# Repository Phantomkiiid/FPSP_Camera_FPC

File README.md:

# FPSP_Camera_FPC
This repo contains FPC schematics of the newly developed FPSP camera project on an FPC board, aiming for super-high-speed parallel image processing.

## Repository Structure
| Directory | Use |
| --------- | --- |
| archive_old/ | Archived initial design (**not working**) |
| custom_fp/ | Footprint from external libraries |
| docs/ | Documentation gathered from external sources |

## TODO
- [ ] RP2350 Power Supply Layout
- [ ] Add Proper Power Sequencing
- [ ] Source RP2354 A4
- [ ] Source B2B Connector
- [ ] B2B Connector Pinout + Layout
- [ ] HSTX Layout

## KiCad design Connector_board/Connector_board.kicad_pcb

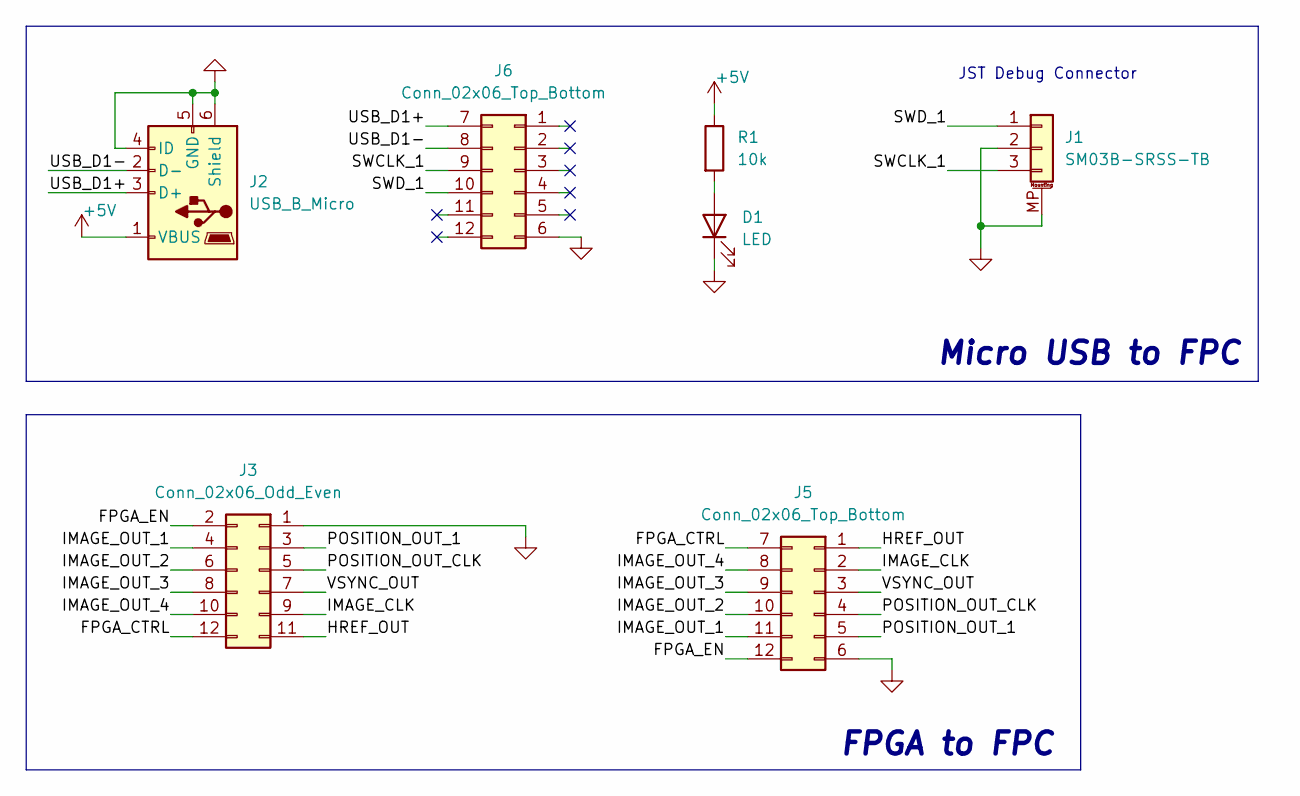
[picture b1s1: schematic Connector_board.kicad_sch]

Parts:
D1: LED; D_0603_1608Metric
J1: SM03B-SRSS-TB; JST_SH_SM03B-SRSS-TB_1x03-1MP_P1.00mm_Horizontal
J2: USB_B_Micro; USB_Micro-B_Molex_47346-0001
J3: Conn_02x06_Odd_Even; PinHeader_2x06_P2.54mm_Vertical
J5, J6: Conn_02x06_Top_Bottom; CON_5035521222
R1: 10k; R_0603_1608Metric_Pad0.98x0.95mm_HandSolder

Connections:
+5V: J2.1 (VBUS), R1.1
/FPGA_CTRL: J3.12, J5.7
/FPGA_EN: J3.2, J5.12
/HREF_OUT: J3.11, J5.1
/IMAGE_CLK: J3.9, J5.2
/IMAGE_OUT_1: J3.4, J5.11
/IMAGE_OUT_2: J3.6, J5.10
/IMAGE_OUT_3: J3.8, J5.9
/IMAGE_OUT_4: J3.10, J5.8
/POSITION_OUT_1: J3.3, J5.5
/POSITION_OUT_CLK: J3.5, J5.4
/SWCLK_1: J1.3, J6.9
/SWD_1: J1.1, J6.10
/USB_D1+: J2.3 (D+), J6.7
/USB_D1-: J2.2 (D-), J6.8
/VSYNC_OUT: J3.7, J5.3
GND: D1.1 (K), J1.2, J1.MP (MountPin), J2.4 (ID), J2.5 (GND), J2.6 (Shield), J3.1, J5.6, J6.6
unnamed: D1.2 (A), R1.2

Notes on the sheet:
FPGA to FPC
Micro USB to FPC
JST Debug Connector

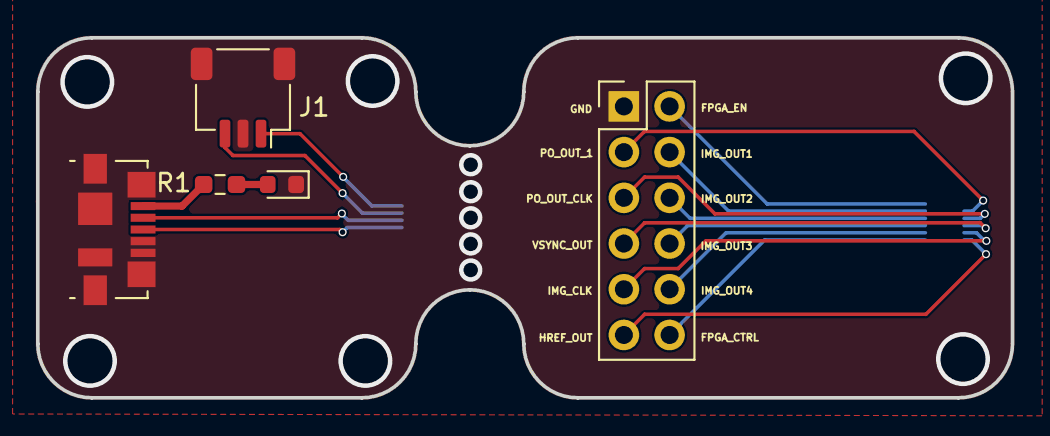
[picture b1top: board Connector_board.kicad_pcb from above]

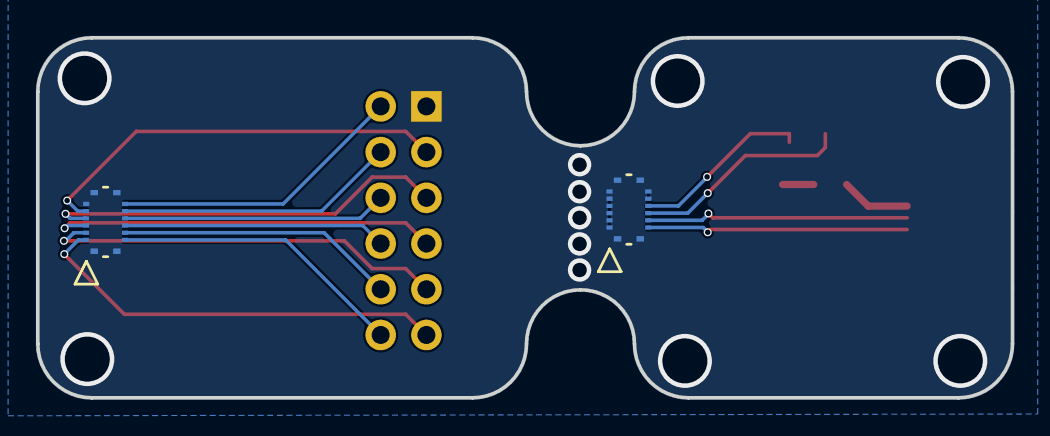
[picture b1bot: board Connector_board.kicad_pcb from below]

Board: 2 copper layers, 54.2 x 20.0 mm, 7 parts (2 on the bottom side), 18 nets.

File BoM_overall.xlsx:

Part Name | Series Number / Description | Quantity | Source | Unit Price (GBP) | Order Code / Mouser No | Link
USB_B_Micro | USB_Micro-B_Molex_47346-0001 | 5 | Farnell | 1.2 | 1568026 | https://uk.farnell.com/molex/47346-0001/micro-usb-conn-2-0-t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
Conn_02x07_Counter_Clockwise | Molex_SlimStack_502426-1430_2x07_P0.40mm_Vertical | 10 | Farnell | 0.86799999999999999 | 3500584 | https://uk.farnell.com/molex/502426-1430/mezzanine-conn-rcpt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
Conn_02x07_Counter_Clockwise | Molex_SlimStack_502430-1430_2x07_P0.40mm_Vertical | 10 | Farnell | 0.46500000000000002 | 3911710 | https://uk.farnell.com/molex/502430-1430/mezzanine-conn-hdr-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
Switch (slide) | CAS-120TA1 | 10 | Farnell | 1.1832 | 2854716 | https://uk.farnell.com/nidec-copal-electronics/cas-120ta/sli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
Push Button | PTS526SM15SMTR2 LFS | 10 | Mouser | 0.12 | 611-PTS526SM15SMTR2L | https://www.mouser.co.uk/ProductDetail/CK/PTS526SM15SMTR2-LF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
SM03B-SRSS-TB | JST_SH_SM03B-SRSS-TB_1x03-1MP_P1.00mm_Horizontal | 5 | Farnell | 0.52 | 1679118 | https://uk.farnell.com/stmicroelectronics/lsm6dsltr/inemo-in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
IMU | LSM6DSLTR | 5 | Farnell | 7.8840000000000003 | 4572492 | https://uk.farnell.com/tdk/icm-45686/mems-module-6-axis-1-71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
LDO | TLV73315PDRV | 5 | Mouser | 0.44 | 595-TLV73315PQDRVRQ1 | https://www.mouser.co.uk/ProductDetail/Texas-Instruments/TLV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
MCU | RP2354A | 5 | Mouser | 0.751 | 358-SC151113 | https://www.mouser.co.uk/ProductDetail/Raspberry-Pi/SC151113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
Mems | SiT8008BI-13-33E-12.000000G | 5 | Mouser | 0.72099999999999997 | 788-8008BI1333E12G | https://www.mouser.co.uk/ProductDetail/SiTime/SiT8008BI-13-3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
FPC socket | molex 52435-2471 | 10 | Farnell | 2.3519999999999999 | 2396220 | https://uk.farnell.com/molex/52435-2471/connector-ffc-fpc-24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
Camera | OV5640 - 24pin fpc | 2 | Ali | N/A | N/A | https://www.aliexpress.com/p/tesla-landing/index.html?UTABTe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
2.54mm pin header: from UCL
0603 R&C: from UCL

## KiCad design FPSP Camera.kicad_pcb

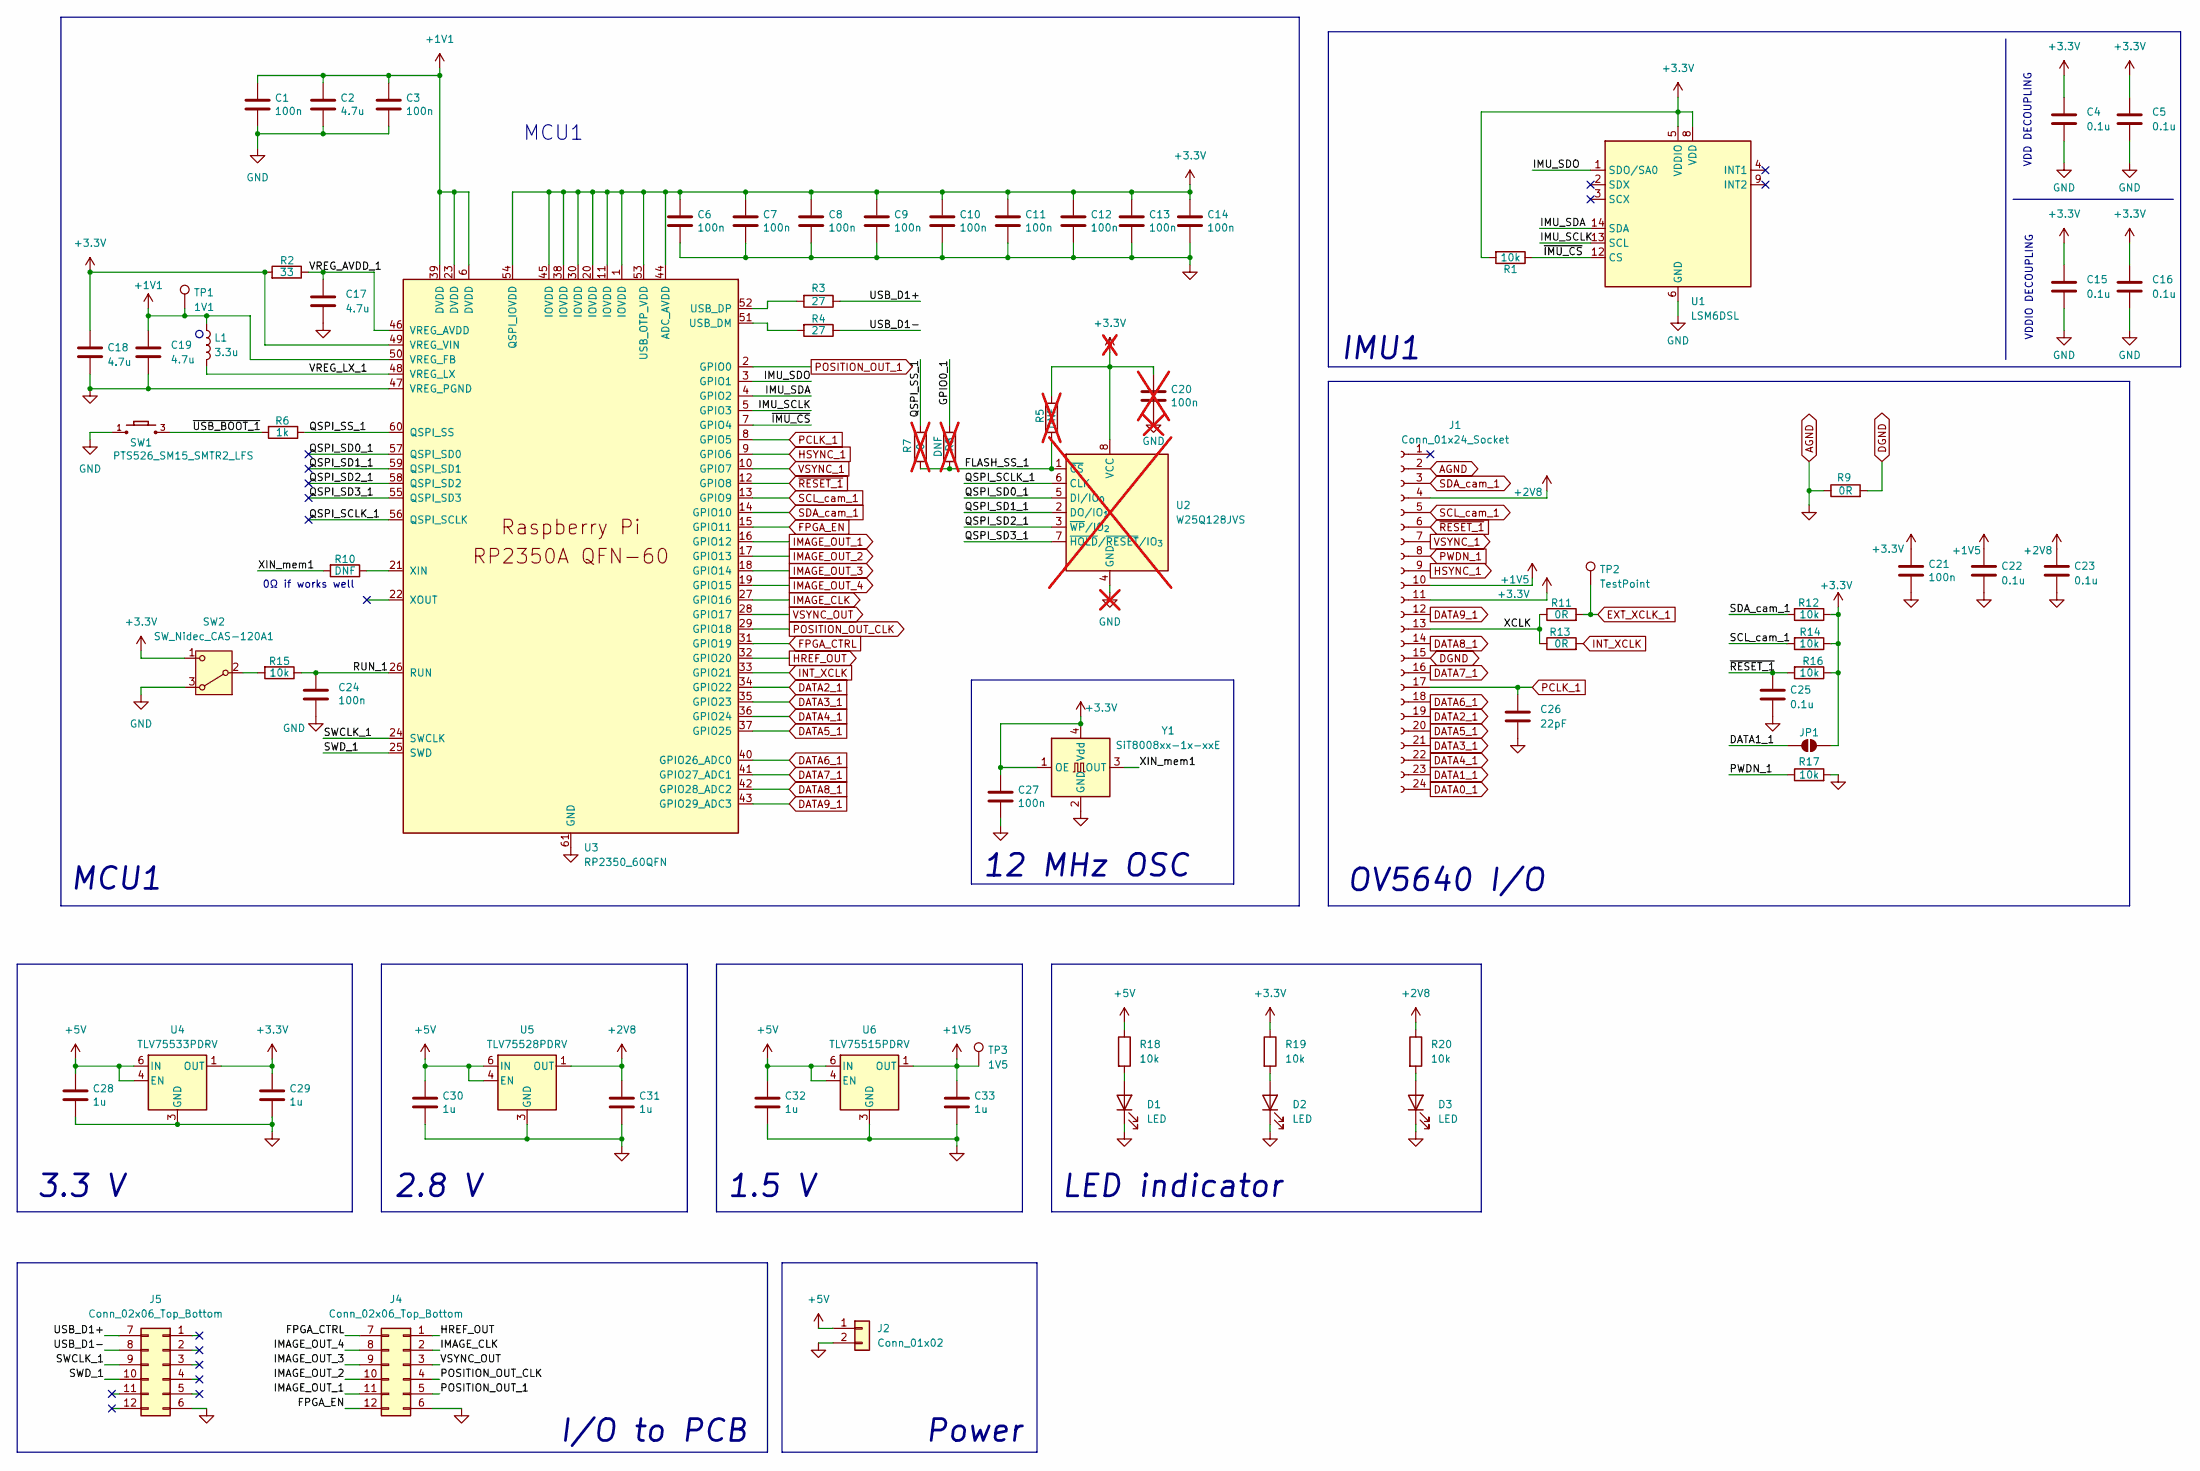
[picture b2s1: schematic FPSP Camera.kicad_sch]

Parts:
C1, C3, C6, C7, C8, C9, C10, C11, C12, C13, C14, C21, C24, C27: 100n; C_0402_1005Metric
C2, C17, C18, C19: 4.7u; C_0402_1005Metric
C4, C5, C15, C16, C22, C23, C25: 0.1u; C_0402_1005Metric
C20: 100n; C_0603_1608Metric_Pad1.08x0.95mm_HandSolder; not fitted
C26: 22pF; C_0402_1005Metric
C28, C29, C30, C31, C32, C33: 1u; C_0402_1005Metric
D1, D2, D3: LED; D_0603_1608Metric
J1: Conn_01x24_Socket; MOLEX_52435-2471
J2: Conn_01x02; PinHeader_1x02_P2.54mm_Vertical
J4, J5: Conn_02x06_Top_Bottom; CON_5035521222
JP1: SolderJumper_2_Open; SolderJumper-2_P1.3mm_Open_RoundedPad1.0x1.5mm
L1: 3.3u; L_pol_2016
R1: 10k; R_0402_1005Metric_Pad0.72x0.64mm_HandSolder
R2: 33; R_0402_1005Metric
R3, R4: 27; R_0402_1005Metric
R5, R8: DNF; R_0603_1608Metric_Pad0.98x0.95mm_HandSolder; not fitted
R6: 1k; R_0402_1005Metric
R7: 0; R_0603_1608Metric_Pad0.98x0.95mm_HandSolder; not fitted
R9, R11, R13: 0R; R_0402_1005Metric
R10: DNF; R_0402_1005Metric
R12, R14, R15, R16, R17, R18, R19, R20: 10k; R_0402_1005Metric
SW1: PTS526_SM15_SMTR2_LFS; PTS526SM15SMTR2LFS; MOUSER_PART_NUMBER 611-PTS526SM15SMTR2L
SW2: SW_Nidec_CAS-120A1; Nidec_Copal_CAS-120A
TP1: 1V1; TestPoint_Pad_D1.0mm
TP2: TestPoint; TestPoint_Pad_D1.0mm
TP3: 1V5; TestPoint_Pad_D1.0mm
U1: LSM6DSL; LGA-14_3x2.5mm_P0.5mm_LayoutBorder3x4y
U2: W25Q128JVS; SOIC-8_5.3x5.3mm_P1.27mm; not fitted
U3: RP2350_60QFN; RP2350-QFN-60-1EP_7x7_P0.4mm_EP3.4x3.4mm_ThermalVias
U4: TLV75533PDRV; WSON-6-1EP_2x2mm_P0.65mm_EP1x1.6mm
U5: TLV75528PDRV; WSON-6-1EP_2x2mm_P0.65mm_EP1x1.6mm
U6: TLV75515PDRV; WSON-6-1EP_2x2mm_P0.65mm_EP1x1.6mm
Y1: SiT8008xx-1x-xxE; Oscillator_SMD_SiT_PQFN-4Pin_2.5x2.0mm

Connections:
+1V1: C1.1, C2.1, C3.1, C19.1, L1.1, TP1.1 (1_1), U3.6 (DVDD), U3.23 (DVDD), U3.39 (DVDD), U3.50 (VREG_FB)
+1V5: C22.1, C33.1, J1.10, TP3.1 (1_1), U6.1 (OUT)
+2V8: C23.1, C31.1, J1.4, R20.1, U5.1 (OUT)
+3.3V: C4.1, C5.1, C6.1, C7.1, C8.1, C9.1, C10.1, C11.1, C12.1, C13.1, C14.1, C15.1, C16.1, C18.1, C20.1, C21.1, C27.1, C29.1, J1.11, JP1.2 (B), R1.2, R2.2, R5.1, R12.1, R14.1, R16.1, R19.1, SW2.1 (C), U1.5 (VDDIO), U1.8 (VDD), U2.8 (VCC), U3.1 (IOVDD), U3.11 (IOVDD), U3.20 (IOVDD), U3.30 (IOVDD), U3.38 (IOVDD), U3.44 (ADC_AVDD), U3.45 (IOVDD), U3.49 (VREG_VIN), U3.53 (USB_OTP_VDD), U3.54 (QSPI_IOVDD), U4.1 (OUT), Y1.1 (OE), Y1.4 (Vdd)
+5V: C28.1, C30.1, C32.1, J2.1, R18.1, U4.4 (EN), U4.6 (IN), U5.4 (EN), U5.6 (IN), U6.4 (EN), U6.6 (IN)
/IMU_SCLK: U1.13 (SCL), U3.5 (GPIO3)
/IMU_SDA: U1.14 (SDA), U3.4 (GPIO2)
/IMU_SDO: U1.1 (SDO/SA0), U3.3 (GPIO1)
/QSPI_SCLK_1: U2.6 (CLK), U3.56 (QSPI_SCLK)
/QSPI_SD0_1: U2.5 (DI/IO_{0}), U3.57 (QSPI_SD0)
/QSPI_SD1_1: U2.2 (DO/IO_{1}), U3.59 (QSPI_SD1)
/QSPI_SD2_1: U2.3 (~WP/IO_{2}), U3.58 (QSPI_SD2)
/QSPI_SD3_1: U2.7 (~HOLD/~RESET/IO_{3}), U3.55 (QSPI_SD3)
/QSPI_SS_1: R6.1, R7.2, U3.60 (QSPI_SS)
/RUN_1: C24.1, R15.1, U3.26 (RUN)
/SWCLK_1: J5.9, U3.24 (SWCLK)
/SWD_1: J5.10, U3.25 (SWD)
/USB_D1+: J5.7, R3.1
/USB_D1-: J5.8, R4.1
/VREG_AVDD_1: C17.1, R2.1, U3.46 (VREG_AVDD)
/VREG_LX_1: L1.2, U3.48 (VREG_LX)
/XCLK: J1.13, R11.1, R13.1
/XIN_mem1: R10.2, Y1.3 (OUT)
/~IMU_CS: R1.1, U1.12 (CS), U3.7 (GPIO4)
/~USB_BOOT_1: R6.2, SW1.3, SW1.4
AGND: C1.2, C2.2, C3.2, C4.2, C5.2, C6.2, C7.2, C8.2, C9.2, C10.2, C11.2, C12.2, C13.2, C14.2, C15.2, C16.2, C17.2, C18.2, C19.2, C20.2, C21.2, C22.2, C23.2, C24.2, C25.2, C26.2, C27.2, C28.2, C29.2, C30.2, C31.2, C32.2, C33.2, D1.1 (K), D2.1 (K), D3.1 (K), J1.2, J1.MP, J2.2, J4.6, J5.6, R9.1, R17.2, SW1.1, SW1.2, SW2.3 (A), U1.6 (GND), U1.7 (GND), U2.4 (GND), U3.47 (VREG_PGND), U3.61 (GND), U4.3 (GND), U4.7 (GND), U5.3 (GND), U5.7 (GND), U6.3 (GND), U6.7 (GND), Y1.2 (GND)
DATA0_1: J1.24
DATA1_1: J1.23, JP1.1 (A)
DATA2_1: J1.19, U3.34 (GPIO22)
DATA3_1: J1.21, U3.35 (GPIO23)
DATA4_1: J1.22, U3.36 (GPIO24)
DATA5_1: J1.20, U3.37 (GPIO25)
DATA6_1: J1.18, U3.40 (GPIO26_ADC0)
DATA7_1: J1.16, U3.41 (GPIO27_ADC1)
DATA8_1: J1.14, U3.42 (GPIO28_ADC2)
DATA9_1: J1.12, U3.43 (GPIO29_ADC3)
DGND: J1.15, R9.2
EXT_XCLK_1: R11.2, TP2.1 (1_1)
FPGA_CTRL: J4.7, U3.31 (GPIO19)
FPGA_EN: J4.12, U3.15 (GPIO11)
HREF_OUT: J4.1, U3.32 (GPIO20)
HSYNC_1: J1.9, U3.9 (GPIO6)
IMAGE_CLK: J4.2, U3.27 (GPIO16)
IMAGE_OUT_1: J4.11, U3.16 (GPIO12)
IMAGE_OUT_2: J4.10, U3.17 (GPIO13)
IMAGE_OUT_3: J4.9, U3.18 (GPIO14)
IMAGE_OUT_4: J4.8, U3.19 (GPIO15)
INT_XCLK: R13.2, U3.33 (GPIO21)
unnamed: D1.2 (A), R18.2
unnamed: D2.2 (A), R19.2
unnamed: D3.2 (A), R20.2
unnamed: R5.2, R7.1, R8.1, U2.1 (~CS)
unnamed: R15.2, SW2.2 (B)
unnamed: R4.2, U3.51 (USB_DM)
unnamed: R3.2, U3.52 (USB_DP)
unnamed: R10.1, U3.21 (XIN)
PCLK_1: C26.1, J1.17, U3.8 (GPIO5)
POSITION_OUT_1: J4.5, U3.2 (GPIO0)
POSITION_OUT_CLK: J4.4, U3.29 (GPIO18)
PWDN_1: J1.8, R17.1
SCL_cam_1: J1.5, R14.2, U3.13 (GPIO9)
SDA_cam_1: J1.3, R12.2, U3.14 (GPIO10)
VSYNC_1: J1.7, U3.10 (GPIO7)
VSYNC_OUT: J4.3, U3.28 (GPIO17)
~RESET_1: C25.1, J1.6, R16.2, U3.12 (GPIO8)

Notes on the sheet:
I/O to PCB
0Ω if works well
IMU1
3.3 V
MCU1
12 MHz OSC
Power
2.8 V
VDD DECOUPLING
LED indicator
1.5 V
VDDIO DECOUPLING
OV5640 I/O

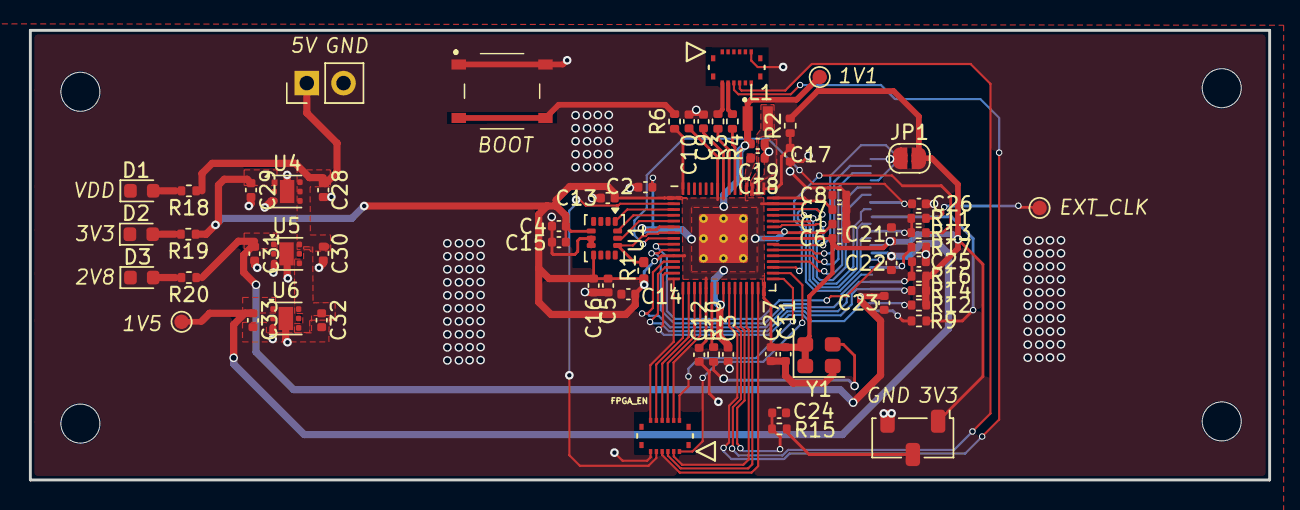
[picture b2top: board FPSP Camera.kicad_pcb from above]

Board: 4 copper layers, 85.7 x 31.1 mm, 73 parts (1 on the bottom side), 58 nets.

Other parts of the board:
H1, H2, H3, H4: MountingHole; MountingHole_2.7mm_M2.5

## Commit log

2025-11-09 Schematics version 1
2025-11-09 minor changes
2025-11-09 pdf version included
2025-11-09 crystal changed to mems
2025-11-10 Hierarchical schematics implemented, with small minor bugs fixed.
2025-11-10 discarded 24MHz crystal. ERC passed 1st time
2025-11-21 updates in layout
2025-11-22 pcb update
2025-11-22 finished the routing
2025-11-22 update schematics - remove one decoupling cap
2025-11-22 layout details finalized for prototype
2025-11-23 vital change to pin order of connector; RP2350 SMPS layout changed
2025-11-23 Documantations updated
2025-11-23 I have tried my best...
2025-11-23 Cleanup
2025-11-23 Reassigned MCU Pinout
2025-11-23 IMU Changed to ICM-45686
2025-11-23 IMU Subsystem Change
2025-11-23 MCU pinout change
2025-11-23 Reannotated schematic
2025-11-23 update MCU layout (initial draft)
2026-06-20 GPIO_1 added
2026-06-23 layout refined
2026-06-23 Rpi Buck layout refined
2026-06-23 push button added; IMU updated
2026-06-24 connector board pin order updated
2026-06-29 new connector footprint updated
2026-06-29 connector footprint swapped
2026-06-30 LDOs replaced
2026-06-30 connector board layout tweaked
